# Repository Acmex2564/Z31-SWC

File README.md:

# Z31-SWC

Reverse engineering of a 1986 Z31's optical steering wheel controls. 

The system consists of 3 components:
* The buttons & transmitter within the wheel
* The slip ring, optical ring, and head amplifier assembly ("clock spring") 
* The reciever, usually located behind the passenger seat

Only the first two subjects are documented here, since I don't have a reciever module. 

The transmitter module reads the values each of the 7 buttons & volume knob, and transmits the information via the slip ring assembly to the head amplifier. The head amplifier buffers the signal and signals to the reciever module, which then controls the radio and ASCD. 

The transmitter module is based on an NEC uPD652C 4-bit microcomputer. 1kbyte ROM, 32 word RAM. It reads & converts the buttons to 12-bit long serial strings, which flash an IR LED in the slip ring assembly. Bit widths are 1ms. 

As I capture them, the frames are laid out as follows:

0-11, from L->R

Resting State: 0101000XXXXX
* Bit 0    : Start of Frame, Always Low ("0" here)
* Bits 1-3 : Cruise Controls
* Bits 4-6 : Media Controls
* Bits 7-11: Volume Control

The actual buttons are:

Cruise Buttons (1-3):
* None	: 101
* Resume	: 011
* Accel	: 010
* Set		: 100

Media Buttons (4-6):
* None	: 000
* SW		: 001
* Tape	: 010
* FM/AM	: 100
* Scan	: 011

The head amplifier is based on an NEC uPC1251 op-amp and phototransistor. Output is made by pulling down the external data line to the reciever assembly. The reciever contains the pullup for this data line. 

The goal of this project is to replace the reciever assembly. The replacement reciever should be able to:
* Control the ASCD (4x 12V active high outputs), 
* Make all outputs available over CAN. 
* Maybe some other analog/resistive SWC outputs?

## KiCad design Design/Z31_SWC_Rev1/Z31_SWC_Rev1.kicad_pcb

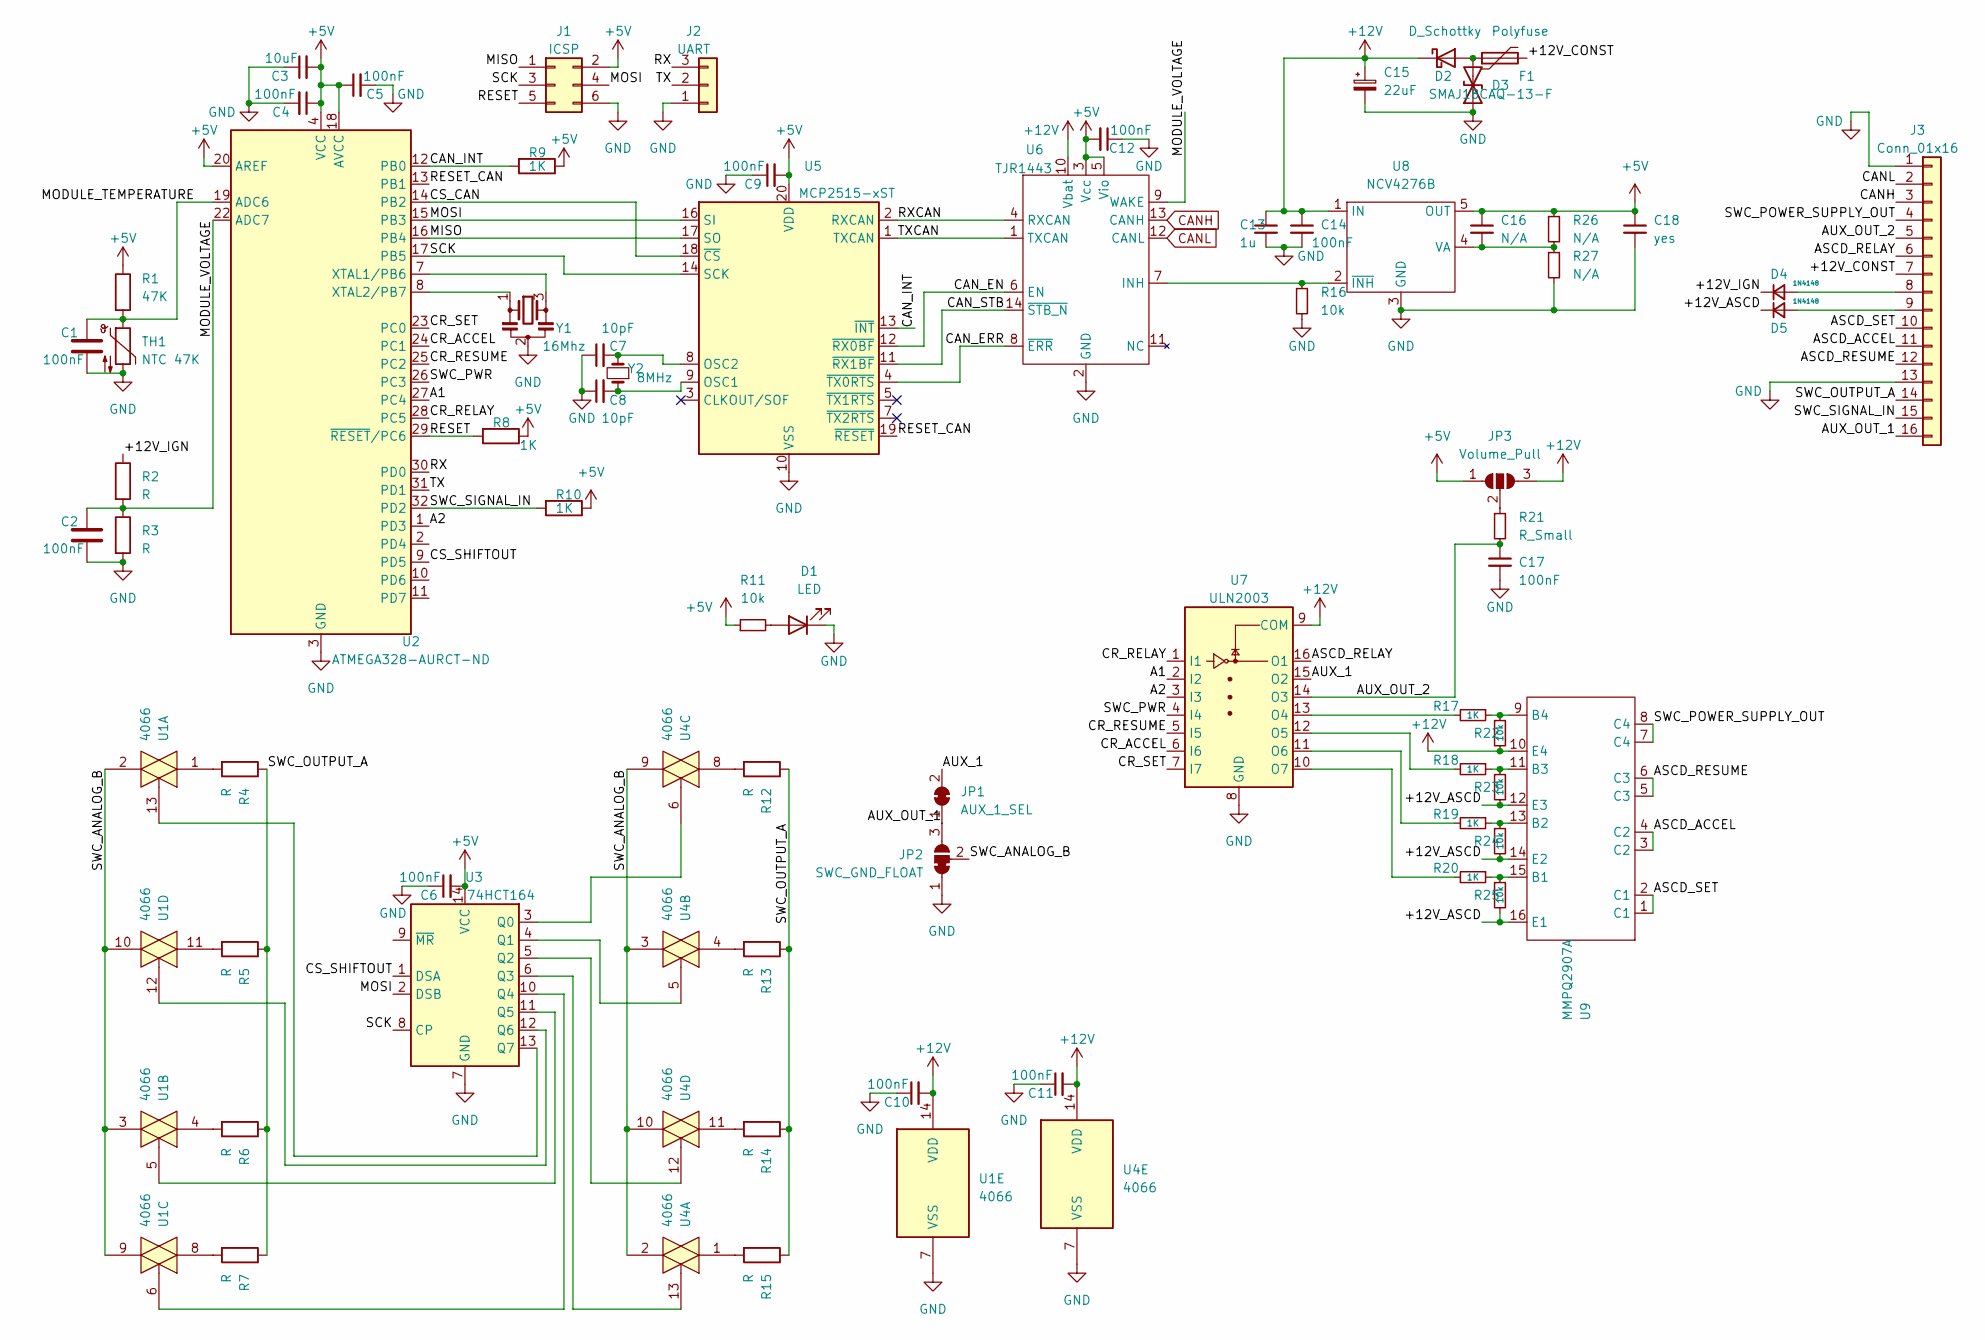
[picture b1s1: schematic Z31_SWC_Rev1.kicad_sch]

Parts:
C1, C2, C4, C5, C6, C9, C10, C11, C12, C14, C17: 100nF; C_0805_2012Metric_Pad1.18x1.45mm_HandSolder
C3: 10uF; CP_Elec_5x5.7
C7, C8: 10pF; C_0805_2012Metric_Pad1.18x1.45mm_HandSolder
C13: 1u; C_1210_3225Metric_Pad1.33x2.70mm_HandSolder
C15: 22uF; CP_Elec_5x5.7
C16: N/A; C_0805_2012Metric_Pad1.18x1.45mm_HandSolder
C18: yes; C_1210_3225Metric_Pad1.33x2.70mm_HandSolder
D1: LED; LED_0805_2012Metric
D2: D_Schottky; D_SMA
D3: SMAJ18CAQ-13-F; D_SMA
D4, D5: 1N4148; D_SOD-323_HandSoldering
F1: Polyfuse; Fuse_1812_4532Metric_Pad1.30x3.40mm_HandSolder
J1: ICSP; PinHeader_2x03_P2.54mm_Vertical
J2: UART; PinHeader_1x03_P2.54mm_Vertical
J3: Conn_01x16; 0348260160
JP1: AUX_1_SEL; SolderJumper-2_P1.3mm_Bridged_Pad1.0x1.5mm
JP2: SWC_GND_FLOAT; SolderJumper-3_P1.3mm_Bridged12_Pad1.0x1.5mm_NumberLabels
JP3: Volume_Pull; SolderJumper-3_P1.3mm_Open_RoundedPad1.0x1.5mm_NumberLabels
R1: 47K; R_0805_2012Metric_Pad1.20x1.40mm_HandSolder
R2, R3: R; R_0805_2012Metric_Pad1.20x1.40mm_HandSolder
R4, R5, R6, R7, R12, R13, R14, R15: R; R_Axial_DIN0207_L6.3mm_D2.5mm_P7.62mm_Horizontal
R8, R9, R10, R17, R18, R19, R20: 1K; R_0805_2012Metric_Pad1.20x1.40mm_HandSolder
R11, R16, R22, R23, R24, R25: 10k; R_0805_2012Metric_Pad1.20x1.40mm_HandSolder
R21: R_Small; R_0805_2012Metric_Pad1.20x1.40mm_HandSolder
R26, R27: N/A; R_0805_2012Metric_Pad1.20x1.40mm_HandSolder
TH1: NTC 47K; R_0805_2012Metric_Pad1.20x1.40mm_HandSolder
U1, U4: 4066; SOIC-14_3.9x8.7mm_P1.27mm
U2: ATMEGA328-AURCT-ND; TQFP-32_7x7mm_P0.8mm
U3: 74HCT164; SOIC-14_3.9x8.7mm_P1.27mm
U5: MCP2515-xST; TSSOP-20_4.4x6.5mm_P0.65mm
U6: TJR1443; SO-14_3.9x8.65mm_P1.27mm
U7: ULN2003; SOIC-16_3.9x9.9mm_P1.27mm
U8: NCV4276B; TO-263-5_TabPin3
U9: MMPQ2907A; SOIC-16_3.9x9.9mm_P1.27mm
Y1: 16Mhz; Resonator_SMD_Murata_CSTxExxV-3Pin_3.0x1.1mm_HandSoldering
Y2: 8MHz; Crystal_SMD_HC49-SD

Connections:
+5V: C3.2, C4.1, C5.1, C6.2, C9.2, C12.2, C16.1, C18.1, J1.2, JP3.1 (A), R1.1, R8.1, R9.1, R10.1, R11.1, R26.1, U2.4 (VCC), U2.6 (VCC), U2.18 (AVCC), U2.20 (AREF), U3.14 (VCC), U5.20 (VDD), U6.3 (Vcc), U6.5 (Vio), U8.5 (OUT)
+12V: C10.2, C11.2, C13.1, C14.1, C15.1, D2.1 (K), JP3.3 (B), R22.2, U1.14 (VDD), U4.14 (VDD), U6.10 (Vbat), U7.9 (COM), U8.1 (IN), U9.10 (E4)
/+12V_ASCD: D5.1 (K), R23.2, R24.2, R25.2, U9.12 (E3), U9.14 (E2), U9.16 (E1)
/+12V_CONST: F1.2, J3.7
/+12V_IGN: D4.1 (K), R2.1
/A1: U2.27 (PC4), U7.2 (I2)
/A2: U2.1 (PD3), U7.3 (I3)
/ASCD_ACCEL: J3.11, U9.3 (C2), U9.4 (C2)
/ASCD_RELAY: J3.6, U7.16 (O1)
/ASCD_RESUME: J3.12, U9.5 (C3), U9.6 (C3)
/ASCD_SET: J3.10, U9.1 (C1), U9.2 (C1)
/AUX_1: JP1.2 (B), U7.15 (O2)
/AUX_OUT_1: J3.16, JP1.1 (A), JP2.3 (B)
/AUX_OUT_2: C17.1, J3.5, R21.2, U7.14 (O3)
/CAN_EN: U5.12 (~RX0BF), U6.6 (EN)
/CAN_ERR: U5.4 (~TX0RTS), U6.8 (~ERR)
/CAN_INT: R9.2, U2.12 (PB0), U5.13 (~INT)
/CAN_STB: U5.11 (~RX1BF), U6.14 (~STB_N)
/CR_ACCEL: U2.24 (PC1), U7.6 (I6)
/CR_RELAY: U2.28 (PC5), U7.1 (I1)
/CR_RESUME: U2.25 (PC2), U7.5 (I5)
/CR_SET: U2.23 (PC0), U7.7 (I7)
/CS_CAN: U2.14 (PB2), U5.18 (~CS)
/CS_SHIFTOUT: U2.9 (PD5), U3.1 (DSA)
/MISO: J1.1, U2.16 (PB4), U5.17 (SO)
/MODULE_TEMPERATURE: C1.1, R1.2, TH1.1, U2.19 (ADC6)
/MODULE_VOLTAGE: C2.1, R2.2, R3.1, U2.22 (ADC7), U6.9 (WAKE)
/MOSI: J1.4, U2.15 (PB3), U3.2 (DSB), U5.16 (SI)
/RESET: J1.5, R8.2, U2.29 (~RESET/PC6)
/RESET_CAN: U2.13 (PB1), U5.19 (~RESET)
/RX: J2.3, U2.30 (PD0)
/RXCAN: U5.2 (RXCAN), U6.4 (RXCAN)
/SCK: J1.3, U2.17 (PB5), U3.8 (CP), U5.14 (SCK)
/SWC_ANALOG_B: JP2.2 (C), U1.2, U1.3, U1.9, U1.10, U4.2, U4.3, U4.9, U4.10
/SWC_OUTPUT_A: J3.14, R4.1, R5.1, R6.1, R7.1, R12.1, R13.1, R14.1, R15.1
/SWC_POWER_SUPPLY_OUT: J3.4, U9.7 (C4), U9.8 (C4)
/SWC_PWR: U2.26 (PC3), U7.4 (I4)
/SWC_SIGNAL_IN: J3.15, R10.2, U2.32 (PD2)
/TX: J2.2, U2.31 (PD1)
/TXCAN: U5.1 (TXCAN), U6.1 (TXCAN)
CANH: J3.3, U6.13 (CANH)
CANL: J3.2, U6.12 (CANL)
GND: C1.2, C2.2, C3.1, C4.2, C5.2, C6.1, C7.1, C8.1, C9.1, C10.1, C11.1, C12.1, C13.2, C14.2, C15.2, C17.2, C18.2, D1.1 (K), D3.1 (A1), J1.6, J2.1, J3.1, J3.13, JP2.1 (A), R3.2, R16.2, R27.2, TH1.2, U1.7 (VSS), U2.3 (GND), U2.5 (GND), U2.21 (GND), U3.7 (GND), U4.7 (VSS), U5.10 (VSS), U6.2 (GND), U7.8 (GND), U8.3 (GND), Y1.2
unnamed: C7.2, U5.8 (OSC2), Y2.2
unnamed: C8.2, U5.9 (OSC1), Y2.1
unnamed: C16.2, R26.2, R27.1, U8.4 (VA)
unnamed: D1.2 (A), R11.2
unnamed: D2.2 (A), D3.2 (A2), F1.1
unnamed: D4.2 (A), J3.8
unnamed: D5.2 (A), J3.9
unnamed: JP3.2 (C), R21.1
unnamed: R4.2, U1.1
unnamed: R5.2, U1.11
unnamed: R6.2, U1.4
unnamed: R7.2, U1.8
unnamed: R12.2, U4.8
unnamed: R13.2, U4.4
unnamed: R14.2, U4.11
unnamed: R15.2, U4.1
unnamed: R16.1, U6.7 (INH), U8.2 (~INH)
unnamed: R17.1, R22.1, U9.9 (B4)
unnamed: R17.2, U7.13 (O4)
unnamed: R18.1, R23.1, U9.11 (B3)
unnamed: R18.2, U7.12 (O5)
unnamed: R19.1, R24.1, U9.13 (B2)
unnamed: R19.2, U7.11 (O6)
unnamed: R20.1, R25.1, U9.15 (B1)
unnamed: R20.2, U7.10 (O7)
unnamed: U1.5, U3.11 (Q5)
unnamed: U1.6, U3.10 (Q4)
unnamed: U1.12, U3.12 (Q6)
unnamed: U1.13, U3.13 (Q7)
unnamed: U2.7 (XTAL1/PB6), Y1.3
unnamed: U2.8 (XTAL2/PB7), Y1.1
unnamed: U3.3 (Q0), U4.6
unnamed: U3.4 (Q1), U4.5
unnamed: U3.5 (Q2), U4.12
unnamed: U3.6 (Q3), U4.13

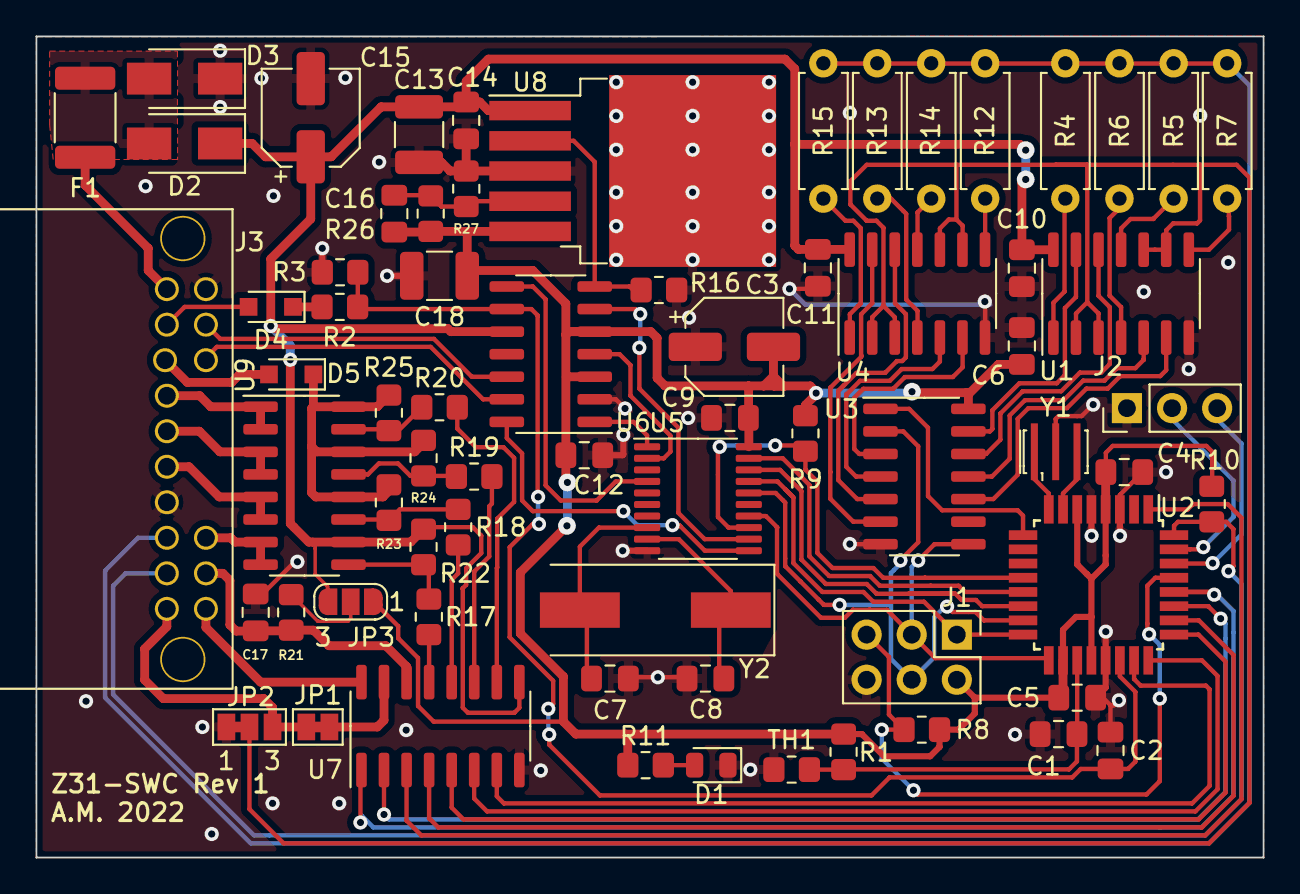
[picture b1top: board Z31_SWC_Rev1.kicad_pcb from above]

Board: 2 copper layers, 69.1 x 46.2 mm, 69 parts (0 on the bottom side), 78 nets.

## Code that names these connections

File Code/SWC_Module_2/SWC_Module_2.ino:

#include <mcp_can.h>
#include <SPI.h>
#include <avr/interrupt.h>
#include <avr/sleep.h>
#include <avr/wdt.h>

#define INPUT_PIN 2
//#define LED_PIN 13
#define BIT_TIME 1000 //microseconds
#define BIT_COUNT 12
#define TIMEOUT 15000 //microseconds
#define PRINT_PERIOD 1000000
#define HISTORY_COUNT 5

#define CAN_INT 8
#define CAN_CS 10

#define SHIFT_CS 5

#define MODULE_TEMP A6
#define MODULE_VOLTAGE A7

#define AUX_OUT_1 18
#define AUX_OUT_2 3 //pwm enabled
#define SWC_POWER 17
#define CRUISE_ACCEL 15 //L/Y --
#define CRUISE_SET 14 //L/OR
#define CRUISE_RESUME 16 //L/G
#define CRUISE_RELAY 19
#define CAN_RESET 9

#define BRIGHTNESS_ID 0x202
#define SWC_ID 0x1D6


volatile bool servicing = false;
int bitCounter = 0;
int serialData[12];
volatile long timeLastFall;
long timeCurrent;
unsigned long timeCurrent2;
long timeLastBit;
long timeLastPrint;
byte pinState;

const byte defaultCruise = 0b00000101;
byte stateCruise         = 0b00000101;

const byte defaultMedia  = 0b00000000;
byte stateMedia          = 0b00000000;

byte stateVolume         = 0b00000000;

bool stateValidButtons = false;

const uint32_t CAN_FREQ = 8000000; // 8 MHz
const uint32_t CAN_RATE = 500000; // 500 kbit/s
MCP_CAN CAN0(CAN_CS);
long unsigned int rxId;
unsigned char len = 0;
unsigned char rxBuf[8];
byte txBufSWC[3];
byte lastBufSWC[3];
char msgString[128];

int histCounter = 0;
int history[3][HISTORY_COUNT];

int histSum[3] = { defaultCruise * HISTORY_COUNT, defaultMedia * HISTORY_COUNT, 0} ;

const int interval_max_ign = 10 * 1000;
long timeLastIgn;
long timeLastCan;
boolean broadcast = false;

const int interval_swc_repeat = 500;
long timeLastSwc;

void setup() {
  // put your setup code here, to run once:
  pinMode(INPUT_PIN, INPUT);
  pinMode(CAN_INT, INPUT);
  pinMode(CAN_CS, OUTPUT);
  pinMode(CAN_RESET, OUTPUT);
  digitalWrite(CAN_RESET, LOW);
  pinMode(SHIFT_CS, OUTPUT);
  pinMode(AUX_OUT_1, OUTPUT);
  pinMode(AUX_OUT_2, OUTPUT);
  pinMode(SWC_POWER, OUTPUT);
  pinMode(CRUISE_ACCEL, OUTPUT);
  pinMode(CRUISE_SET, OUTPUT);
  pinMode(CRUISE_RESUME, OUTPUT);
  pinMode(CRUISE_RELAY, OUTPUT);


  Serial.begin(115200);
  Serial.println("Alive");


  for (int i = 0; i <= (HISTORY_COUNT - 1); i++) {
    history[0][i] = defaultCruise;
    history[1][i] = defaultMedia;
    history[2][i] = 0;
  }


  digitalWrite(CAN_RESET, HIGH);
  delay(10);

  if (CAN0.begin(MCP_ANY, CAN_500KBPS, MCP_8MHZ) == CAN_OK)
  {
    Serial.println("MCP2515 Initialized Successfully!");
  }
  else
  {
    Serial.println("Error Initializing MCP2515...");
  }
  CAN0.setMode(MCP_NORMAL);
  // set can transciever into normal mode
  CAN0.setGPO(0b00000011); //EN and STB HIGH

  attachInterrupt(digitalPinToInterrupt(INPUT_PIN), interrupt_svc, FALLING);
  digitalWrite(SWC_POWER, HIGH);

  wdt_enable(WDTO_8S);
  Serial.println("Awaiting SWC");
}

void loop() {
  // put your main code here, to run repeatedly:
  timeCurrent = micros();
  //Serial.println(((analogRead(MODULE_VOLTAGE)*5/1023.0 * ((35.7+90) / 35.7))));

  if (servicing) {

    if (timeCurrent - timeLastBit >= BIT_TIME) {
      //      digitalWrite(LED_PIN, HIGH);
      pinState = digitalRead(INPUT_PIN);
      //      digitalWrite(LED_PIN, LOW);
      if (pinState == HIGH) {
        serialData[bitCounter] = 1;
      }
      else {
        serialData[bitCounter] = 0;
      }
      bitCounter++;
      timeLastBit = timeCurrent;
    }

    //If the char has been filled, or if the timeout period has elapsed, reset to nothing
    if  ((bitCounter >= BIT_COUNT) || ((timeCurrent - timeLastFall) >= TIMEOUT)) {
      servicing = false;

      if (bitCounter == BIT_COUNT) {

        bitWrite(stateCruise, 2, serialData[1]);
        bitWrite(stateCruise, 1, serialData[2]);
        bitWrite(stateCruise, 0, serialData[3]);

        bitWrite(stateMedia, 2, serialData[4]);
        bitWrite(stateMedia, 1, serialData[5]);
        bitWrite(stateMedia, 0, serialData[6]);

        stateVolume = 0;

        bitWrite(stateVolume, 4, serialData[7]);
        bitWrite(stateVolume, 3, serialData[8]);
        bitWrite(stateVolume, 2, serialData[9]);
        bitWrite(stateVolume, 1, serialData[10]);
        bitWrite(stateVolume, 0, serialData[11]);

        stateVolume = map(stateVolume, 0, 32, 100, 0);

        stateValidButtons = true;
      }
      if ((timeCurrent - timeLastFall) >= TIMEOUT) {
        Serial.println("Timeout");
        stateCruise = defaultCruise;
        stateMedia = defaultMedia;
        stateValidButtons = true;
      }
      bitCounter = 0;
    }

  }

  //canbus shit goes here
  else {
    if ((analogRead(MODULE_VOLTAGE)*5/1023.0 * ((35.7+90) / 35.7)) > 10.0) {
      timeLastIgn = millis(); 
    }

    if (((millis() - timeLastIgn > interval_max_ign) && (millis() - timeLastCan > interval_max_ign )) || (millis() - timeLastIgn > 5 * interval_max_ign)) {
      poweroff();
    }

    if (millis() - timeLastIgn < interval_max_ign/2) {
      broadcast = true;
    }
    else {
      broadcast = false;
    }
      

    if (stateValidButtons) {

      histSum[0] = (histSum[0] - history[0][histCounter]) + stateCruise;
      history[0][histCounter] = stateCruise;
      histSum[1] = (histSum[1] - history[1][histCounter]) + stateMedia;
      history[1][histCounter] = stateMedia;
      histSum[2] = (histSum[2] - history[2][histCounter]) + stateVolume;
      history[2][histCounter] = stateVolume;
      //Serial.println(histCounter);
      //Serial.print(history[0][0]); Serial.print(history[0][1]); Serial.print(history[0][2]); Serial.print(history[0][3]); Serial.println(history[0][4]);
      //Serial.println(histSum[0]);
      if (histCounter >= (HISTORY_COUNT - 1))
      {
        histCounter = 0;
      }
      else
      {
        histCounter++;
      }

      if ((stateVolume == (histSum[2] / HISTORY_COUNT )) & (stateMedia == (histSum[1] / HISTORY_COUNT)) & (stateCruise == (histSum[0] / HISTORY_COUNT)))
      {
        txBufSWC[1] = stateMedia;
        txBufSWC[2] = stateVolume;
        txBufSWC[0] = stateCruise;
      }
      else
      {
        //Serial.println("History Mismatch.");
        //Serial.print(stateVolume); Serial.println(histSum[2] / HISTORY_COUNT);
        //Serial.print(stateMedia); Serial.println(histSum[1] / HISTORY_COUNT);
        //Serial.print(stateCruise); Serial.println(histSum[0] / HISTORY_COUNT);
        //Serial.println();

        txBufSWC[1] = defaultMedia;
        txBufSWC[2] = defaultCruise;
        stateCruise = defaultCruise;

      }


      if (((txBufSWC[0] != lastBufSWC[0]) || (txBufSWC[1] != lastBufSWC[1]) || (txBufSWC[2] != lastBufSWC[2]) || (millis() - timeLastSwc > interval_swc_repeat)) && broadcast)
      {
        if (CAN0.sendMsgBuf(SWC_ID, 0, 3, txBufSWC) == CAN_OK) {
          lastBufSWC[0] = txBufSWC[0];
          lastBufSWC[1] = txBufSWC[1];
          lastBufSWC[2] = txBufSWC[2];
          timeLastSwc = millis();
        }
        else {
          Serial.println("Tx SWC Failure");
          Serial.println(CAN0.sendMsgBuf(SWC_ID, 0, 3, txBufSWC));
        }
        
      }

      if (stateCruise == defaultCruise) {
        digitalWrite(CRUISE_ACCEL, LOW);
        digitalWrite(CRUISE_SET, LOW);
        digitalWrite(CRUISE_RESUME, LOW);
      }
      else if (stateCruise == 0b00000010) {
        digitalWrite(CRUISE_ACCEL, HIGH);
        digitalWrite(CRUISE_SET, LOW);
        digitalWrite(CRUISE_RESUME, LOW);
        Serial.println("Cruise Accel Pressed!");
      }
      else if (stateCruise == 0b00000011) {
        digitalWrite(CRUISE_ACCEL, LOW);
        digitalWrite(CRUISE_SET, LOW);
        digitalWrite(CRUISE_RESUME, HIGH);
        Serial.println("Cruise Resume Pressed!");
      }
      else if (stateCruise == 0b00000100) {
        digitalWrite(CRUISE_ACCEL, LOW);
        digitalWrite(CRUISE_SET, HIGH);
        digitalWrite(CRUISE_RESUME, LOW);
        Serial.println("Cruise Set Pressed!");
      }
      else {
        digitalWrite(CRUISE_ACCEL, LOW);
        digitalWrite(CRUISE_SET, LOW);
        digitalWrite(CRUISE_RESUME, LOW);
      }

      stateValidButtons = false;
    }

    //read for brightness message
    if (!digitalRead(CAN_INT))
    {
      CAN0.readMsgBuf(&rxId, &len, rxBuf);
      timeLastCan = millis();

      if (rxId == 0x202) {
        Serial.print("Recv'd brightness msg: ");

        for (byte i = 0; i < len; i++) {
          sprintf(msgString, "0x%.2x", rxBuf[i]);
          Serial.print(msgString);
        }
        Serial.println();
                
        if (rxBuf[0] == 0xFE) {
          analogWrite(AUX_OUT_2, 0xFF);
        }
        else {
          analogWrite(AUX_OUT_2, map(rxBuf[0], 0x0, 0xFD, 0xFF, 0x0));
        }

      }
    }
  }
wdt_reset();
}

void poweroff() {
  Serial.println("Poweroff");
  digitalWrite(SWC_POWER, LOW);
  CAN0.setGPO(0b00000001);
  delay(1000);
  //set_sleep_mode(SLEEP_MODE_PWR_DOWN);
  //cli();
  //sleep_mode();
}

void interrupt_svc() {

  servicing = true;
  timeLastFall = micros();
  delayMicroseconds(BIT_TIME / 2);
}

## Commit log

2022-04-08 Final Rev1 design
2022-05-29 add code to repository
2022-09-29 Catchup Commit
2023-05-21 Attemped SWC sleep/wake fix (module still slightly insomniac when battery voltage is low???)
2023-05-21 Drop kicad_prl
